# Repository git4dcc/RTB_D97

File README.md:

# RTB_D97

## This is a [opendcc](https://forum.opendcc.de/viewtopic.php?t=10857) forum project
**Unleash your Homebrew DCC Function Decoder projects!**<br><br>
This repository provides a high-performance, **compiled firmware** tailored for the Microchip AVR64DA32 (see the pinout below!). I provide the digital brain — the rest is up to you. While essential support circuitry (power, dividers, level shifters) is required, this design choice is intentionally open, **inviting you** to innovate and customize your ultimate DCC decoder hardware. Scroll down for starter schematics and explore my other repos for more circuit ideas!

:star2: This decoder offers the distinctive capability of controlling up to **32 WS2811 NeoPixel LEDs**, facilitating simple LED wiring.

**User Guides**

- [User Guide - DE](https://rtb4dcc.de/rtb_fndecoder_Reference_de/)
- [User Guide - EN](https://rtb4dcc.de/rtb_fndecoder_Reference_en/)

The setup shows the CPU interfaced with the DCC signal (orange wires), a Railcom transmitter (dark blue wire), and a wire to a heartbeat LED. Standard power (VDD/GND) lines are also there. The PCB located on the right holds all the necessary support electronics, including the power supply management and voltage level shifters. The detailed schematic for this board is available in the [RTB_P26 GitHub repository](/../../../../git4dcc/RTB_P26).
<br><br>

## Decoder firmware features
- **DCC**
  - DCC-A support (incl. Preamble fingerprint)
  - DCC-R support (DCC extension)
  - Service Mode Programming (Programming track)
  - Support of 'long 0000' programming address
- **Railcom**
  - Channel 1/2
  - jitter free
  - programmable TSS1, TSS2 timing
  - POM, xPOM
  - DYN: QoS, Track-Voltage, Temperatur and more
- **I/O ports**
  - 10 AUX ports total (6 ports with 93kHz hardware PWM)
  - 32 LED ports
    - either (SR: 74HC595) or (WS: WS2811/WS2812) mode
  - One 10-bit analog output port (0-5V)
  - Two 12-bit analog input ports (0-5V)
  - SUSI port (5V)
  - Servo port
- **Automation**
  - light emulation (bulb, neon, mars, ditch, ...)
  - Port automation (head-/taillight, engine room, driver cabin, ...)
- **General**
  - buffer capacitor control
  - CPU heartbeat LED for status information
  - fast firmware update on main tracks via DCC-R
- **DCC protocol statistic reporting**
  - DCC bit timing
  - DCC frame rate

# Hardware
The application targets the AVR64DA32 microcontroller. For assembly, the TQFP package is available and can be hand-soldered quite easily by someone with a little experience. For machine assembly, the smaller VQFN package is the preferred choice.

As expected, the microcontroller's built-in I/O is restricted to standard logic levels and the VDD voltage range. Since DCC signals require a different voltage level, external drivers or level translators are necessary to ensure the device can interface with the DCC bus.

## Pinout

| pin | label | direction | description |
| --- | --- | --- | --- |
| PA0 | F0r | output | Front light (rear) (/w hardware pwm) |
| PA1 | F0f | output | Front light (front) (/w hardware pwm) |
| PA2 | AUX1 | output | Auxiliary port 1 (/w hardware pwm) |
| PA3 | AUX2 | output | Auxiliary port 2 (/w hardware pwm) |
| PA4 | AUX3 | output | Auxiliary port 3 (/w hardware pwm) |
| PA5 | AUX4 | output | Auxiliary port 4 (/w hardware pwm) |
| PA6 | AUX5 | output | Auxiliary port 5 |
| PA7 | AUX6 | output | Auxiliary port 6 |
| PC0 | WS28xx | output | WS: DO / SR: data |
| PC1 | DCC-a | input | DCC input (left track) |
| PC2 | AUX7 | output | Auxiliary port 7 / SR: SHCP |
| PC3 | AUX8 | output | Auxiliary port 8 / SR: STCP |
| PD0 | uDCC-a | input | analog track voltage measure (left track) |
| PD1 | uDCC-b | input | analog track voltage measure (right track) |
| PD2 | iAUX | input | analog AUX current measure |
| PD3 | IN1 | input | analog input 1 |
| PD4 | IN2 | input | analog input 2 |
| PD5 | ACK | output | Service mode ACK current generator pin |
| PD6 | DAC_out | output | Analog output voltage |
| PD7 | CAP_ena | output | Buffer capacity control |
| PF0 | Servo_dat | output | Servo data |
| PF1 | Servo_pwr | output | Servo power control |
| PF2 | SUSI_sda | output | SUSI data |
| PF3 | SUSI_scl | output | SUSI clock |
| PF4 | Railcom | output | Railcom transmitter |
| PF5 | LED.hbt | output | Hearbeat LED |
| PF6 | DCC-b | input | DCC input (right track) |
| UPDI | UPDI | in/out | Programming pin |

## Kicad
<details>
  
<br>
This GitHub repository contains only the schematic. A PCB layout is not included, as the physical board design is intended to be customized and completed by each user.
<br><br>

[Schematic](doc/D97_schematic.pdf)

</details>

## Firmware
<details>
<br>
Initial firmware load must be done by using a UPDI programmer. Subsequent software updates can be done by using the RTB layout control infrastructure.
<br><br>
  
Filename structure: { **pcb** }{ **code** }{ **version** }.hex

Example: **D97F0001**.hex

|   | Description |
| --- | --- |
| **pcb** | Name of matching hardware (**D97**) |
| **code** | Type of code contained (**R**=rom, **B**=bootloader, **F**=flash, **U**=bld update, **P**=UPDI factory code) |
| **version** | Release version (**####**) |

[Firmware files](firmware)

## UPDI / Fuses
The fuse settings as well as the P-code (D97Pxxxx.hex) has to be installed by using UPDI.<br>

| Fuses Setting |
| --- |
||

</details>

# Building blocks
Below the supporting electronics that can be used to construct DCC decoders with various functions and capabilities. These examples are offered only as suggestions and are designed to be fully customizable to meet specific needs.

| CPU only | /w Service Mode | /w Railcom |
| --- | --- | --- |
|  |  |  |

| external LED ports |
| --- |
|  |
<br>

# Examples
Below some examples of different Decoder designs. Starting from very simple up to fully featured.
<br><br>
  
## Example 1
This represents the **most basic DCC decoder design**. It requires only a power source and the DCC voltage divider to operate. All functional ports, as previously described, are available at standard logic voltage levels.

- _Note: The pulldown resistors have proven to be a good investment for DCC/Railcom reliability. I recommend to have them always there._

## Example 2
This example builds upon Example 1 by adding the essential capability of reading Configuration Variables (CVs) on the programming track. All other specifications and requirements remain the same as in the first example.

## Example 3
This example extends Example 2 by integrating Railcom (Bi-Directional Communication) capability. This powerful addition enables several advanced functions, including Programming on the Main (PoM), DCC-A, DCC-R, and firmware updates directly via the main track. All basic specifications and requirements remain unchanged from Example 1.

- _Note: I am also adding the track voltage divider so the decoder can report **track voltage** via Railcom correctly_

## Example 4
Here a simple but powerful NeoPixel Decoder that commands up to 32 WS28xx LEDs. Whether you prefer the control of WS2811 driver chips or the simplicity of integrated RGB LEDs like the WS2812C, this decoder is your lighting maestro.

- _Note 1: Here VDD must be set to 5V because most WS28xx chips only run reliably with 5V._
- _Note 2: I highly recommend opting for the low-current (5mA) versions of the WS28xx chips otherwise the decoder would be drawing some serious current if all LEDs are at full brightness!_

# Images
Some pictures of my prototype(s)
| /w two WS2812 RGB leds | /w sixteen WS2811 leds |
| --- | --- |
|  |  |

# YouTube
Showcased here are various decoder projects utilizing this DCC decoder toolkit. The accompanying PCBs are generally custom-designed to address specific functional and physical demands.<br><br>
| Video: H0 Roco /w RGB leds |
| --- |
|  |

This project is intended for hobby use only and is distributed in accordance with the Apache License 2.0 agreement.

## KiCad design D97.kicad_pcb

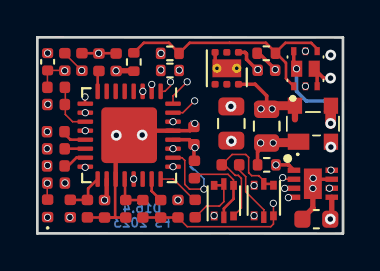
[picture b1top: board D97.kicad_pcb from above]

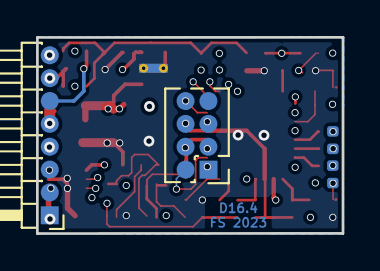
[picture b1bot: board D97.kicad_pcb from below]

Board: 6 copper layers, 17.0 x 10.9 mm, 43 parts (4 on the bottom side), 42 nets.

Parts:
C1, C3, C13: 22u/4V; C_0402_1005Metric
C2: 100u/4V; C_0805_2012Metric
C4: 1u/35V; C_0603_1608Metric
C6: 1u; C_0402_1005Metric
C7: 22u/25V; C_0805_2012Metric
D1: LED; LED_0402_1005Metric
D3: BAS3007ARPPE6327HTSA1; BF998215
IC1: DRV8231ADSGR; SON50P200X200X80-9N
IC2: NCP730BMT330TBG; WSON-6-1EP_2x2mm_P0.65mm_EP1x1.6mm_ThermalVias
J1: Service IF; PinHeader_2x04_P1.27mm_Vertical
J2: NEM651; PinHeader_1x08_P1.27mm_Horizontal
Q1: BC857BDW1; SOT-666
Q2: BC847BDW1; SOT-666
Q3: SSM6N55NU; CSD87502Q2
R1, R2: 3.3k; R_0402_1005Metric
R3: 22; R_0402_1005Metric
R4, R5, R6: 2.2k; R_0402_1005Metric
R7, R8, R10, R12: 33k; R_0402_1005Metric
R9, R22: 2.2; R_0402_1005Metric
R11, R13, R15, R18, R19, R20: 10k; R_0402_1005Metric
R14, R16: dummy; R_0402_1005Metric
R17, R34, R35: 220k; R_0402_1005Metric
R21: 1k; R_0402_1005Metric
R36, R37: 9.1k; R_0402_1005Metric
U1: AVR-64DA32; VQFN-32-1EP_5x5mm_P0.5mm_EP3.1x3.1mm

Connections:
+3V3: C1.2, C2.1, C3.1, C13.2, IC2.1, J1.4, Q1.1, R3.1, U1.18, U1.28
AUX1: R6.1, U1.13
AUX2: R4.1, U1.14
AUX3: R5.1, U1.15
DCC-a: D3.3, J2.5, Q2.3, R7.1, R19.2, R34.1
DCC-b: D3.2, J2.4, Q2.6, R8.1, R20.2, R35.1
F0f: Q3.5, U1.1
F0r: Q3.2, U1.32
GND: C1.1, C2.2, C3.2, C4.2, C6.2, C7.2, C13.1, D1.1, D3.1, IC1.7, IC1.9, IC2.3, IC2.7, J1.6, J2.8, Q2.4, R2.1, R9.1, R11.1, R13.1, R19.1, R20.1, R22.1, R36.2, R37.2, U1.19, U1.29, U1.33
IFL: R21.2, U1.12
ISENS: C6.1, R17.2, U1.21
LED.hbt: R1.1, U1.9
Lf: J2.7, Q3.3, Q3.D2
Lr: J2.6, Q3.6, Q3.D1
M1: IC1.8, J2.3, R12.2
M2: IC1.6, J2.2, R10.2
unnamed: D1.2, R1.2, R16.2
unnamed: IC1.1, R2.2, R17.1
unnamed: Q1.2, Q1.4, R3.2
unnamed: Q1.3, Q2.1, Q2.2, R18.2
unnamed: Q1.5, Q1.6, R15.2
unnamed: Q2.5, R18.1
unnamed: Q3.1, Q3.4, R9.2, R21.1, R22.2
unnamed: R7.2, U1.8
unnamed: R8.2, U1.23
unnamed: R6.2, R14.1
unnamed: R4.2, R14.2
unnamed: R5.2, R16.1
PWM1: IC1.2, U1.2
PWM2: IC1.3, U1.3
RCM.tx: R15.1, U1.24
UDCC-a: R34.2, R36.1, U1.10
UDCC-b: R35.2, R37.1, U1.20
UPDI: J1.3, U1.27
V24.cts: J1.2, U1.26
V24.rts: J1.1, U1.25
V24.rx: J1.8, U1.31
V24.tx: J1.5, U1.30
VHBR: C4.1, C7.1, D3.4, IC1.5, IC2.6, J2.1
Vref: IC1.4, U1.16
uSENS1: R12.1, R13.2, U1.11
uSENS2: R10.1, R11.2, U1.17

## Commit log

2025-11-22 Fix punctuation and wording in README.md
2026-02-20 Fix link to RTB_P26 GitHub repository in README
    Updated the link to the RTB_P26 GitHub repository for accuracy.
2026-02-20 git mirror test
2026-02-22 Update README with forum project badge and links
    Added forum project badge and updated Kicad_Libs link in README.

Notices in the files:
D97.kicad_pcb:
Licensed under the Apache License, Version 2
